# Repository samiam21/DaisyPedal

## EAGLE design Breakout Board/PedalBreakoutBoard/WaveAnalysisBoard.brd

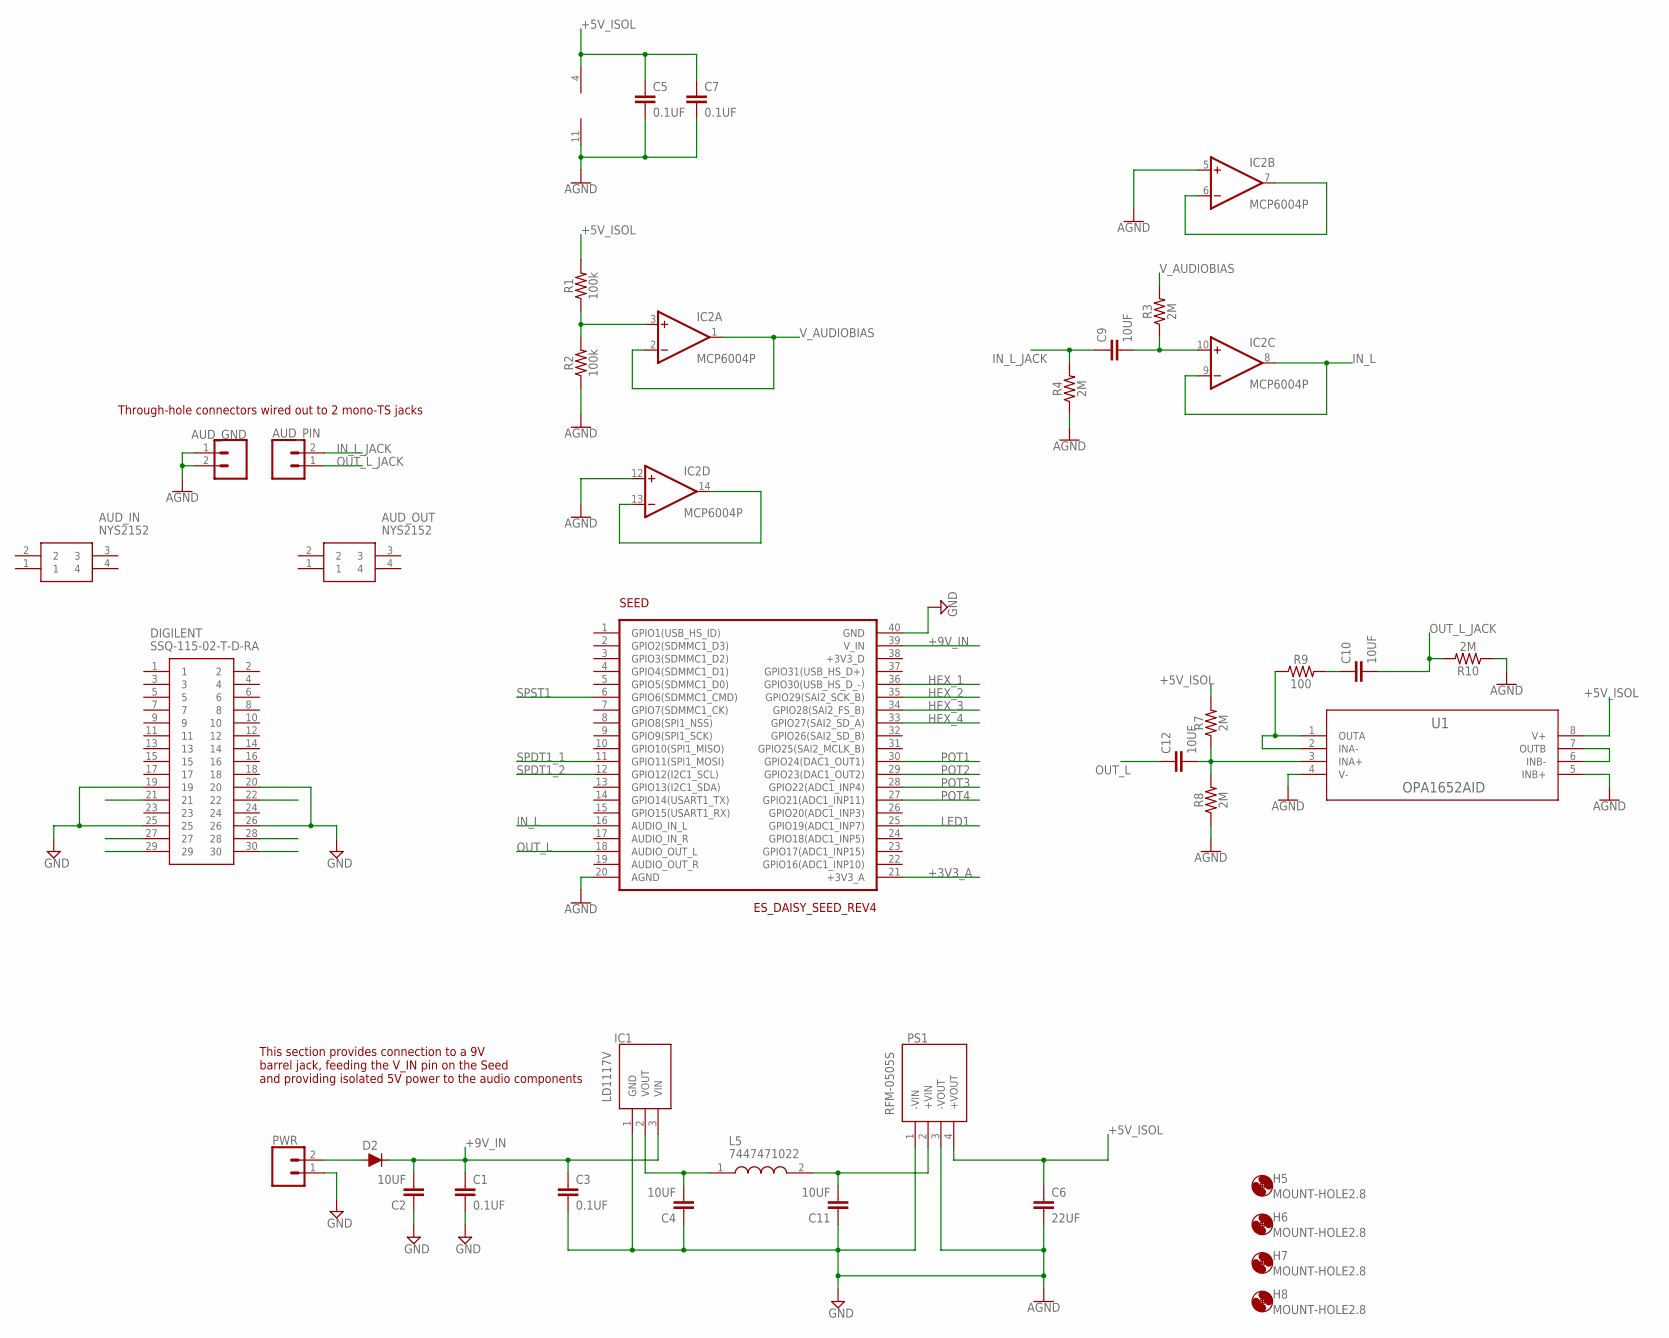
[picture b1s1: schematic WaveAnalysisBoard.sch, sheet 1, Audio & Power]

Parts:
AUD_GND: CONN_02; 1X02
AUD_IN: NYS2152
AUD_OUT: NYS2152
AUD_PIN: CONN_02; 1X02
C1, C3, C5, C7: 0.1UF; CAP-PTH-SMALL-KIT
C2, C4, C9, C10, C11, C12: 10UF; CAP-PTH-SMALL-KIT
C6: 22UF; CAP-PTH-SMALL-KIT
D2: 200mA/100V/1V; DIODE-1N4148
DIGILENT: SSQ-115-02-T-D-RA; RHDRRA30W64P254_2X15_3861X851X
H5, H6, H7, H8: MOUNT-HOLE2.8; 2,8
IC1: LD1117V; TO255P460X1020X2008-3P
IC2: MCP6004P; DIL14
L5: 7447471022; WE-TIS_111190
PS1: RFM-0505S; RFM0505S
PWR: CONN_02; 1X02
R1, R2: 100k; AXIAL-0.3
R3, R4, R7, R8, R10: 2M; AXIAL-0.3
R9: 100; AXIAL-0.3
SEED: ES_DAISY_SEED_REV4; ES_DAISY_SEED
U1: OPA1652AID; D8

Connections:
+3V3_A: SEED.21 (+3V3_A); also elsewhere on the board
+5V_ISOL: C5.1, C6.1, C7.1, IC2.4 (V+), PS1.4 (+VOUT), R1.P$2 (2), R7.P$2 (2), U1.8 (V+)
+9V_IN: C1.1, C2.2, C3.1, D2.C, IC1.3 (VIN), SEED.39 (V_IN)
AGND: AUD_GND.1, AUD_GND.2, C3.2, C4.1, C5.2, C6.2, C7.2, C11.1, IC1.1 (GND), IC2.5 (+IN), IC2.11 (V-), IC2.12 (+IN), PS1.1 (-VIN), PS1.3 (-VOUT), R2.P$1 (1), R4.P$1 (1), R8.P$1 (1), R10.P$1 (1), SEED.20 (AGND), U1.4 (V-), U1.5 (INB+)
GND: C1.2, C2.1, DIGILENT.19, DIGILENT.20, DIGILENT.25, DIGILENT.26, PWR.1, SEED.40 (GND); also elsewhere on the board
HEX_1: SEED.36 (GPIO30(USB_HS_D_-)); also elsewhere on the board
HEX_2: SEED.35 (GPIO29(SAI2_SCK_B)); also elsewhere on the board
HEX_3: SEED.34 (GPIO28(SAI2_FS_B)); also elsewhere on the board
HEX_4: SEED.33 (GPIO27(SAI2_SD_A)); also elsewhere on the board
IN_L: IC2.8 (OUT), IC2.9 (-IN), SEED.16 (AUDIO_IN_L)
IN_L_JACK: AUD_PIN.2, C9.1, R4.P$2 (2)
LED1: SEED.25 (GPIO19(ADC1_INP7)); also elsewhere on the board
unnamed: D2.A, PWR.2
unnamed: IC2.3 (+IN), R1.P$1 (1), R2.P$2 (2)
unnamed: C11.2, L5.2, PS1.2 (+VIN)
unnamed: C4.2, IC1.2 (VOUT), L5.1
unnamed: C9.2, IC2.10 (+IN), R3.P$1 (1)
unnamed: IC2.13 (-IN), IC2.14 (OUT)
unnamed: C12.2, R7.P$1 (1), R8.P$2 (2), U1.3 (INA+)
unnamed: R9.P$1 (1), U1.1 (OUTA), U1.2 (INA-)
unnamed: C10.1, R9.P$2 (2)
unnamed: U1.6 (INB-), U1.7 (OUTB)
unnamed: IC2.6 (-IN), IC2.7 (OUT)
OUT_L: C12.1, SEED.18 (AUDIO_OUT_L)
OUT_L_JACK: AUD_PIN.1, C10.2, R10.P$2 (2)
POT1: SEED.30 (GPIO24(DAC1_OUT1)); also elsewhere on the board
POT2: SEED.29 (GPIO23(DAC1_OUT2)); also elsewhere on the board
POT3: SEED.28 (GPIO22(ADC1_INP4)); also elsewhere on the board
POT4: SEED.27 (GPIO21(ADC1_INP11)); also elsewhere on the board
SPDT1_1: SEED.11 (GPIO11(SPI1_MOSI)); also elsewhere on the board
SPDT1_2: SEED.12 (GPIO12(I2C1_SCL)); also elsewhere on the board
SPST1: SEED.6 (GPIO6(SDMMC1_CMD)); also elsewhere on the board
V_AUDIOBIAS: IC2.1 (OUT), IC2.2 (-IN), R3.P$2 (2)

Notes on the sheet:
Through-hole connectors wired out to 2 mono-TS jacks
This section provides connection to a 9V barrel jack, feeding the V_IN pin on the Seed and providing isolated 5V power to the audio components

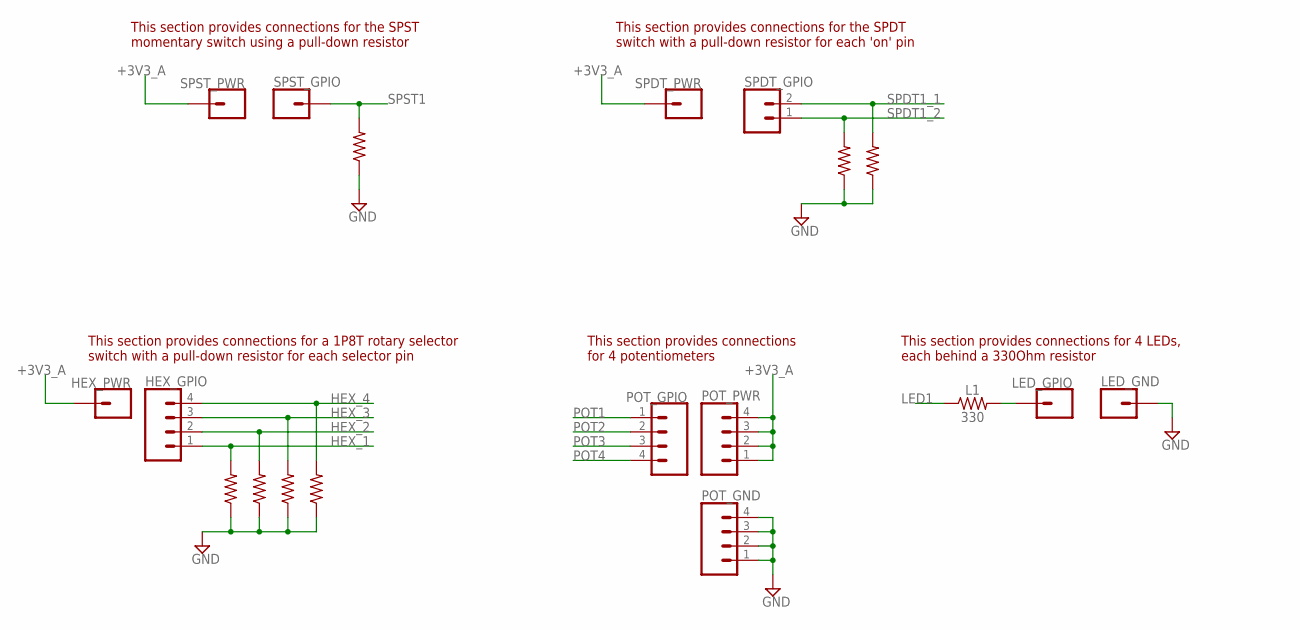
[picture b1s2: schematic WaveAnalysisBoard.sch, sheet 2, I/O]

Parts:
D11, D12: 10k; AXIAL-0.3
H1, H2, H3, H4: 10k; AXIAL-0.3
HEX_GPIO: CONN_04; 1X04
HEX_PWR: CONN_01; 1X01
L1: 330; AXIAL-0.3
LED_GND: CONN_01; 1X01
LED_GPIO: CONN_01; 1X01
POT_GND: CONN_04; 1X04
POT_GPIO: CONN_04; 1X04
POT_PWR: CONN_04; 1X04
S1: 10k; AXIAL-0.3
SPDT_GPIO: CONN_02; 1X02
SPDT_PWR: CONN_01; 1X01
SPST_GPIO: CONN_01; 1X01
SPST_PWR: CONN_01; 1X01

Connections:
+3V3_A: HEX_PWR.1, POT_PWR.1, POT_PWR.2, POT_PWR.3, POT_PWR.4, SPDT_PWR.1, SPST_PWR.1; also elsewhere on the board
GND: D11.P$1 (1), D12.P$1 (1), H1.P$1 (1), H2.P$1 (1), H3.P$1 (1), H4.P$1 (1), LED_GND.1, POT_GND.1, POT_GND.2, POT_GND.3, POT_GND.4, S1.P$1 (1); also elsewhere on the board
HEX_1: H1.P$2 (2), HEX_GPIO.1; also elsewhere on the board
HEX_2: H2.P$2 (2), HEX_GPIO.2; also elsewhere on the board
HEX_3: H3.P$2 (2), HEX_GPIO.3; also elsewhere on the board
HEX_4: H4.P$2 (2), HEX_GPIO.4; also elsewhere on the board
LED1: L1.P$1 (1); also elsewhere on the board
unnamed: L1.P$2 (2), LED_GPIO.1
POT1: POT_GPIO.1; also elsewhere on the board
POT2: POT_GPIO.2; also elsewhere on the board
POT3: POT_GPIO.3; also elsewhere on the board
POT4: POT_GPIO.4; also elsewhere on the board
SPDT1_1: D11.P$2 (2), SPDT_GPIO.2; also elsewhere on the board
SPDT1_2: D12.P$2 (2), SPDT_GPIO.1; also elsewhere on the board
SPST1: S1.P$2 (2), SPST_GPIO.1; also elsewhere on the board

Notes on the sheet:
This section provides connections for the SPDT switch with a pull-down resistor for each 'on' pin
This section provides connections for a 1P8T rotary selector switch with a pull-down resistor for each selector pin
This section provides connections for 4 potentiometers
This section provides connections for the SPST momentary switch using a pull-down resistor
This section provides connections for 4 LEDs, each behind a 330Ohm resistor

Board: 2 copper layers, 55 parts (0 on the bottom side), 34 nets, no tracks yet.

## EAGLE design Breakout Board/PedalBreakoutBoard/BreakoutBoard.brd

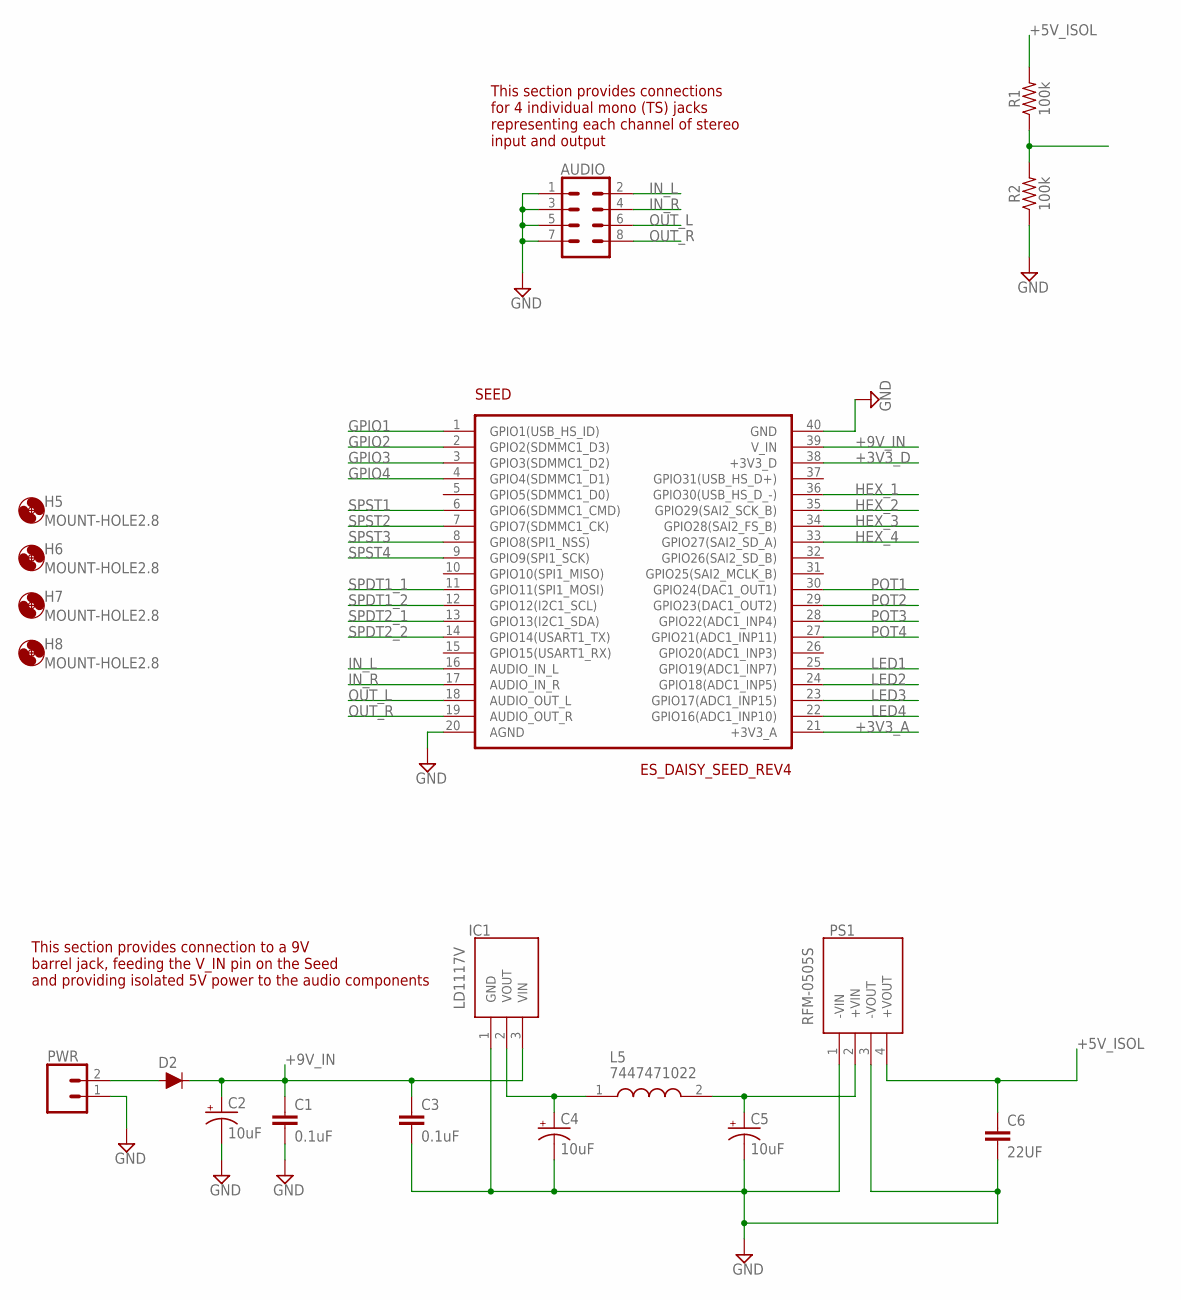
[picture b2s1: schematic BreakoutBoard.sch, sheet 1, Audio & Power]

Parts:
AUDIO: CONN_04X2; 2X4
C1, C3: 0.1uF; CAP-PTH-SMALL-KIT
C2, C4, C5: 10uF; CPOL-RADIAL-2.5MM-5MM
C6: 22UF; CAP-PTH-SMALL-KIT
D2: 200mA/100V/1V; DIODE-1N4148
H5, H6, H7, H8: MOUNT-HOLE2.8; 2,8
IC1: LD1117V; TO255P460X1020X2008-3P
L5: 7447471022; WE-TIS_111190
PS1: RFM-0505S; RFM0505S
PWR: CONN_02; 1X02
R1, R2: 100k; AXIAL-0.3
SEED: ES_DAISY_SEED_REV4; ES_DAISY_SEED

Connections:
+3V3_A: SEED.21 (+3V3_A); also elsewhere on the board
+3V3_D: SEED.38 (+3V3_D)
+5V_ISOL: C6.1, PS1.4 (+VOUT), R1.P$2 (2)
+9V_IN: C1.1, C2.1 (+), C3.1, D2.C, IC1.3 (VIN), SEED.39 (V_IN)
GND: AUDIO.1, AUDIO.3, AUDIO.5, AUDIO.7, C1.2, C2.2 (-), C3.2, C4.2 (-), C5.2 (-), C6.2, IC1.1 (GND), PS1.1 (-VIN), PS1.3 (-VOUT), PWR.1, R2.P$1 (1), SEED.20 (AGND), SEED.40 (GND); also elsewhere on the board
GPIO1: SEED.1 (GPIO1(USB_HS_ID)); also elsewhere on the board
GPIO2: SEED.2 (GPIO2(SDMMC1_D3)); also elsewhere on the board
GPIO3: SEED.3 (GPIO3(SDMMC1_D2)); also elsewhere on the board
GPIO4: SEED.4 (GPIO4(SDMMC1_D1)); also elsewhere on the board
HEX_1: SEED.36 (GPIO30(USB_HS_D_-)); also elsewhere on the board
HEX_2: SEED.35 (GPIO29(SAI2_SCK_B)); also elsewhere on the board
HEX_3: SEED.34 (GPIO28(SAI2_FS_B)); also elsewhere on the board
HEX_4: SEED.33 (GPIO27(SAI2_SD_A)); also elsewhere on the board
IN_L: AUDIO.2, SEED.16 (AUDIO_IN_L)
IN_R: AUDIO.4, SEED.17 (AUDIO_IN_R)
LED1: SEED.25 (GPIO19(ADC1_INP7)); also elsewhere on the board
LED2: SEED.24 (GPIO18(ADC1_INP5)); also elsewhere on the board
LED3: SEED.23 (GPIO17(ADC1_INP15)); also elsewhere on the board
LED4: SEED.22 (GPIO16(ADC1_INP10)); also elsewhere on the board
unnamed: D2.A, PWR.2
unnamed: R1.P$1 (1), R2.P$2 (2)
unnamed: C5.1 (+), L5.2, PS1.2 (+VIN)
unnamed: C4.1 (+), IC1.2 (VOUT), L5.1
OUT_L: AUDIO.6, SEED.18 (AUDIO_OUT_L)
OUT_R: AUDIO.8, SEED.19 (AUDIO_OUT_R)
POT1: SEED.30 (GPIO24(DAC1_OUT1)); also elsewhere on the board
POT2: SEED.29 (GPIO23(DAC1_OUT2)); also elsewhere on the board
POT3: SEED.28 (GPIO22(ADC1_INP4)); also elsewhere on the board
POT4: SEED.27 (GPIO21(ADC1_INP11)); also elsewhere on the board
SPDT1_1: SEED.11 (GPIO11(SPI1_MOSI)); also elsewhere on the board
SPDT1_2: SEED.12 (GPIO12(I2C1_SCL)); also elsewhere on the board
SPDT2_1: SEED.13 (GPIO13(I2C1_SDA)); also elsewhere on the board
SPDT2_2: SEED.14 (GPIO14(USART1_TX)); also elsewhere on the board
SPST1: SEED.6 (GPIO6(SDMMC1_CMD)); also elsewhere on the board
SPST2: SEED.7 (GPIO7(SDMMC1_CK)); also elsewhere on the board
SPST3: SEED.8 (GPIO8(SPI1_NSS)); also elsewhere on the board
SPST4: SEED.9 (GPIO9(SPI1_SCK)); also elsewhere on the board

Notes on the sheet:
This section provides connections for 4 individual mono (TS) jacks representing each channel of stereo input and output
This section provides connection to a 9V barrel jack, feeding the V_IN pin on the Seed and providing isolated 5V power to the audio components

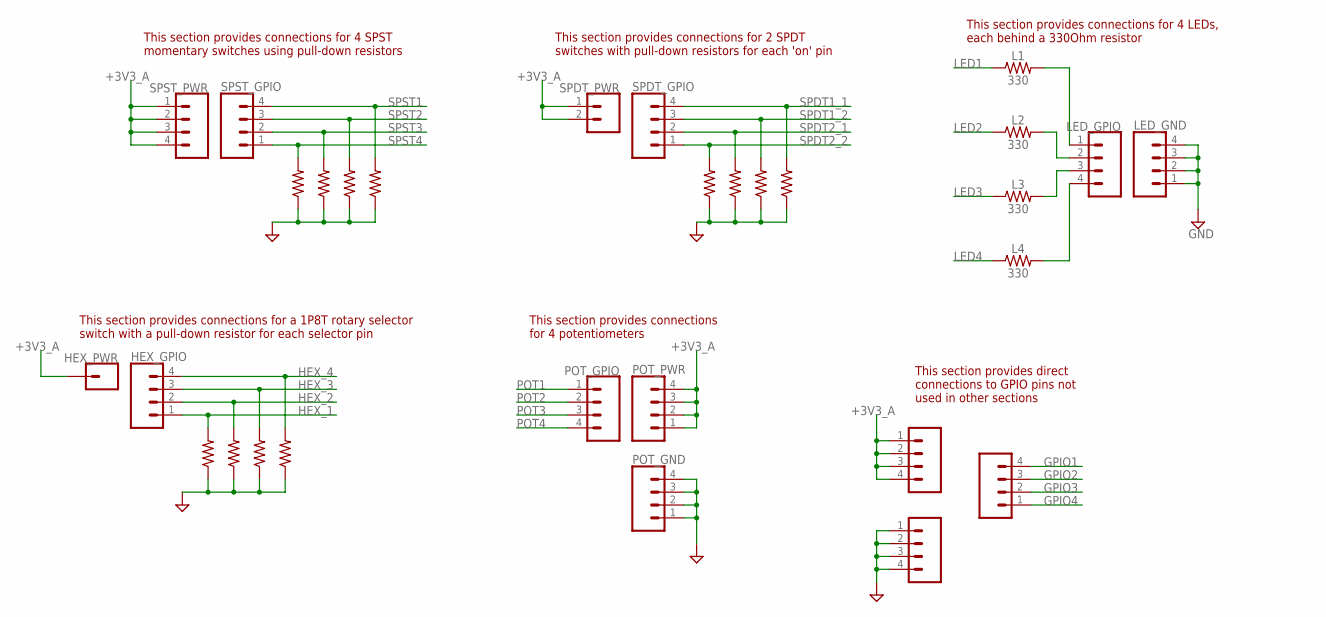
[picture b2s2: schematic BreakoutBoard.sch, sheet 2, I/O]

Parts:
D11, D12, D21, D22: 10k; AXIAL-0.3
EX_GND: CONN_04; 1X04
EX_GPIOS: CONN_04; 1X04
EX_PWR: CONN_04; 1X04
H1, H2, H3, H4: 10k; AXIAL-0.3
HEX_GPIO: CONN_04; 1X04
HEX_PWR: CONN_01; 1X01
L1, L2, L3, L4: 330; AXIAL-0.3
LED_GND: CONN_04; 1X04
LED_GPIO: CONN_04; 1X04
POT_GND: CONN_04; 1X04
POT_GPIO: CONN_04; 1X04
POT_PWR: CONN_04; 1X04
S1, S2, S3, S4: 10k; AXIAL-0.3
SPDT_GPIO: CONN_04; 1X04
SPDT_PWR: CONN_02; 1X02
SPST_GPIO: CONN_04; 1X04
SPST_PWR: CONN_04; 1X04

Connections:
+3V3_A: EX_PWR.1, EX_PWR.2, EX_PWR.3, EX_PWR.4, HEX_PWR.1, POT_PWR.1, POT_PWR.2, POT_PWR.3, POT_PWR.4, SPDT_PWR.1, SPDT_PWR.2, SPST_PWR.1, SPST_PWR.2, SPST_PWR.3, SPST_PWR.4; also elsewhere on the board
GND: D11.P$1 (1), D12.P$1 (1), D21.P$1 (1), D22.P$1 (1), EX_GND.1, EX_GND.2, EX_GND.3, EX_GND.4, H1.P$1 (1), H2.P$1 (1), H3.P$1 (1), H4.P$1 (1), LED_GND.1, LED_GND.2, LED_GND.3, LED_GND.4, POT_GND.1, POT_GND.2, POT_GND.3, POT_GND.4, S1.P$1 (1), S2.P$1 (1), S3.P$1 (1), S4.P$1 (1); also elsewhere on the board
GPIO1: EX_GPIOS.4; also elsewhere on the board
GPIO2: EX_GPIOS.3; also elsewhere on the board
GPIO3: EX_GPIOS.2; also elsewhere on the board
GPIO4: EX_GPIOS.1; also elsewhere on the board
HEX_1: H1.P$2 (2), HEX_GPIO.1; also elsewhere on the board
HEX_2: H2.P$2 (2), HEX_GPIO.2; also elsewhere on the board
HEX_3: H3.P$2 (2), HEX_GPIO.3; also elsewhere on the board
HEX_4: H4.P$2 (2), HEX_GPIO.4; also elsewhere on the board
LED1: L1.P$1 (1); also elsewhere on the board
LED2: L2.P$1 (1); also elsewhere on the board
LED3: L3.P$1 (1); also elsewhere on the board
LED4: L4.P$1 (1); also elsewhere on the board
unnamed: L1.P$2 (2), LED_GPIO.1
unnamed: L2.P$2 (2), LED_GPIO.2
unnamed: L3.P$2 (2), LED_GPIO.3
unnamed: L4.P$2 (2), LED_GPIO.4
POT1: POT_GPIO.1; also elsewhere on the board
POT2: POT_GPIO.2; also elsewhere on the board
POT3: POT_GPIO.3; also elsewhere on the board
POT4: POT_GPIO.4; also elsewhere on the board
SPDT1_1: D11.P$2 (2), SPDT_GPIO.4; also elsewhere on the board
SPDT1_2: D12.P$2 (2), SPDT_GPIO.3; also elsewhere on the board
SPDT2_1: D21.P$2 (2), SPDT_GPIO.2; also elsewhere on the board
SPDT2_2: D22.P$2 (2), SPDT_GPIO.1; also elsewhere on the board
SPST1: S1.P$2 (2), SPST_GPIO.4; also elsewhere on the board
SPST2: S2.P$2 (2), SPST_GPIO.3; also elsewhere on the board
SPST3: S3.P$2 (2), SPST_GPIO.2; also elsewhere on the board
SPST4: S4.P$2 (2), SPST_GPIO.1; also elsewhere on the board

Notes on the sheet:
This section provides connections for 2 SPDT switches with pull-down resistors for each 'on' pin
This section provides connections for a 1P8T rotary selector switch with a pull-down resistor for each selector pin
This section provides connections for 4 potentiometers
This section provides connections for 4 SPST momentary switches using pull-down resistors
This section provides connections for 4 LEDs, each behind a 330Ohm resistor
This section provides direct connections to GPIO pins not used in other sections

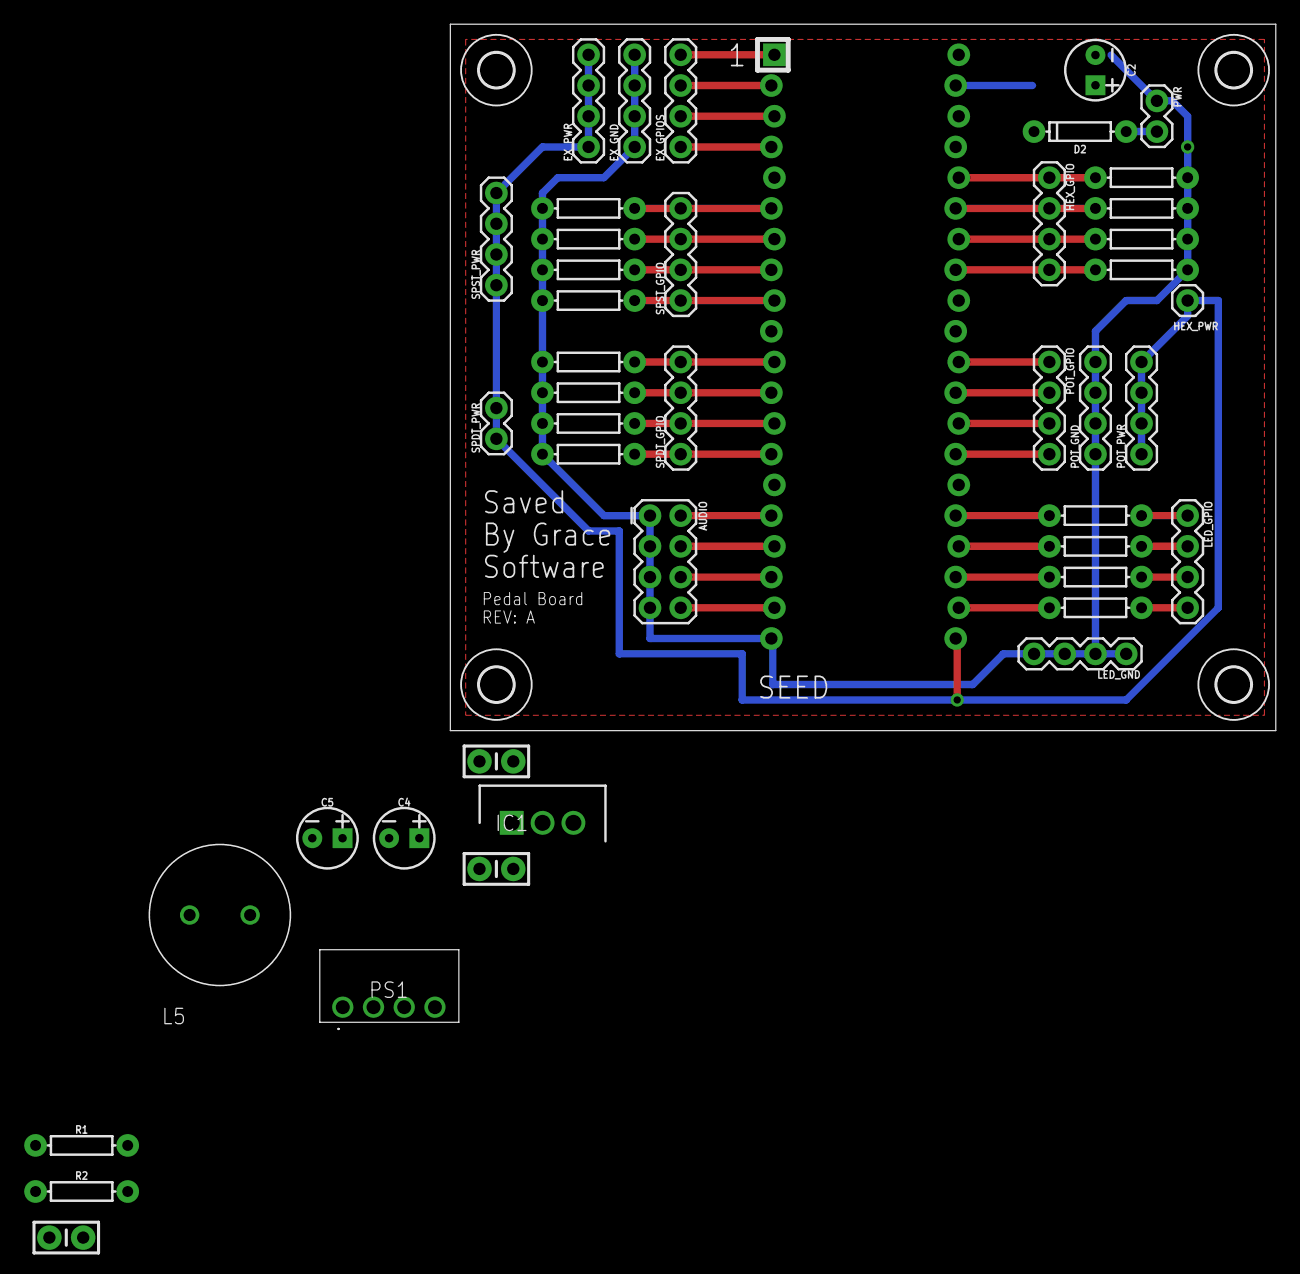
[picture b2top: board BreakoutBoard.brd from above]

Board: 2 copper layers, 68.2 x 58.4 mm, 49 parts (0 on the bottom side), 40 nets.

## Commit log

2020-09-08 DP-9 - Add StereoDelay example
2020-09-08 DP-9 - Stereo delay disabled with button press
2020-09-08 DP-9 - Add bypass example and mono starting point
2020-09-08 DP-9 - Update mono to use single channel
2020-09-11 DP-9 - Add audacity test project
2020-09-20 DP-9 - Fix issue with long verify times
2020-09-20 DP-9 - Disable auto-formatting for this workspace
2020-09-20 DP-9 - Turn delay on/off with a switch
2020-10-01 DP-9 - Add toggle of LED for delay on/off
2020-10-01 DP-10 - Set delay tempo in BPM
2020-10-02 DP-10 - Cleanup and adding timespan formula to comments
2020-10-02 DP-12 - Add initial connectors notes
2020-10-02 DP-12 - Move testing audio into subfolder
2020-10-03 DP-12 - Add base app
2020-10-03 DP-12 - Reference mono delay from pedal app
2020-10-03 DP-12 - Enable effect based on hex switch
2020-10-03 DP-12 - Clean up mono delay
2020-10-03 DP-12 - Fix startup to enable bypass
2020-10-03 DP-12 - Update pins for switch
2020-10-07 DP-10 - Add debug serial printing
2020-10-07 DP-10 - Add button press to light LED for mono delay
2020-10-07 DP-10 - Fix hex switch reading
2020-10-08 DP-10 - Calculate time between button presses
2020-10-08 DP-10 - Add include path for desktop
2020-10-08 DP-10 - Adding tempo array class
2020-10-08 DP-10 - Working on reorganizing project structure
2020-10-09 DP-10 - Move MonoDelay files into subdirectory
2020-10-09 DP-10 - Add HWDebug effect type
2020-10-09 DP-10 - Fix calculation of tempo
2020-10-09 DP-10 - Merge bypass and hwdebug to reduce memory usage
2020-10-09 DP-10 - Code cleanup
2020-10-09 Update the README
2020-10-14 DP-11 - Add handling and testing of pots
2020-10-14 DP-11 - Working on reading decay knob
2020-10-14 DP-11 - Read decay knob
2020-10-14 DP-11 - Move decay knob reading parameter
2020-10-17 DP-11 - Adjust decay with knob
2020-10-17 DP-11 - Add possible future effect types
2020-10-17 DP-14 - Add level control
2020-10-17 DP-14 - Switch level and decay knobs
2020-10-17 DP-14 - Update comments
2020-10-17 DP-15 - Add definitions in comments
2020-10-18 DP-16 - Add base project and daisy library
2020-10-18 DP-16 - Add empty schematic
2020-10-19 DP-16 - Adding audio connectors
2020-10-19 DP-16 - Add grounds
2020-10-19 DP-16 - Add audio molex
2020-10-19 DP-16 - Add LED molex
2020-10-19 DP-16 - Update LED molex
2020-10-19 DP-16 - Add SPST molex
2020-10-19 DP-16 - Update board in/out
2020-10-19 DP-16 - Change molex connectors to through holes
2020-10-19 DP-16 - Move connections into groups
2020-10-19 DP-16 - Add SPDT section
2020-10-19 DP-16 - Reorder groups for consistency
2020-10-20 DP-16 - Add selector section
2020-10-21 DP-16 - Update schematic to add new sheet
2020-10-21 DP-16 - Update schematic with correct 3V3 feeds
2020-10-21 DP-16 - Add power section
2020-10-21 DP-16 - Fix nets
2020-10-21 DP-16 - Working on board layout
2020-10-22 DP-16 - Board layout REV-A
2020-10-22 DP-16 - Board layout REV-B
2020-10-22 DP-16 - Initial routing
2020-10-22 DP-16 - Update board layout
2020-10-22 DP-16 - Working on silkscreen and mounting holes
2020-10-22 DP-16 - Updating to through hole parts
2020-10-22 DP-16 - Update firmware to handle gray coded rotary switch
2020-10-22 Working on adding mounting holes
2020-10-23 DP-16 - Update capacitors to through hole components
2020-10-25 DP-16 - Add mounting holes
2020-10-26 DP-16 - Move Daisy to edge
2020-10-26 DP-16 - Shrink board
2020-10-26 DP-15 - Updating pin definitions
2020-10-27 DP-15 - Update pin definitions
2020-10-27 DP-15 - Add example of using a class function as the daisy callback
2020-10-28 DP-15 - Convert effects to classes
2020-10-28 DP-15 - Use effect interface for pedal loop
2020-10-28 DP-15 - Add SPDT test to bypass
2020-10-28 DP-15 - Remove monodelay to make this a template
2020-10-28 DP-20 - Update copper pour
2020-10-28 DP-20 - Move covered label
2020-11-05 Remove putty link
2020-11-11 Convert to platformio
2020-11-11 DP-24 - Working on converting to interrupts
2020-11-12 DP-24 - Change selector to interrupt and fix serial printing
2020-11-12 Auto-update of cpp properties by platform io
2020-11-18 Updating pinout to match new pcb
2020-11-18 Fix encoder reading
2020-11-18 Fix selector interrupts
2020-11-19 Add ability to bypass effect selector
2020-11-19 Fix bypassing of effect selector
2020-11-20 Ignoring .vscode files
2020-11-22 Add knob class
2020-11-23 Fix knob class
2020-11-24 Add button handler class
2020-11-24 Update HWTest to use button and knob classes
2020-11-24 Add toggle class
2020-12-08 DP-33 - Added power section
2020-12-08 DP-33 - Add custom library and 22uf capacitor
2020-12-08 DP-33 - Add remaining audio noise schematic
2020-12-08 DP-33 - Add MonoPedal schematic
2020-12-08 DP-33 - Ignore backup files for Eagle
2020-12-08 DP-34 - Working on board layout
2020-12-10 Working on board layout
2020-12-10 DP-34 - First draft board layout complete
2020-12-10 DP-34 - Fixing silk screen errors
2020-12-11 DP-35 - Fix selector by switching back to polling
2020-12-23 DP-33 - Update breakout board with ceramic capacitors
2020-12-23 DP-33 - Update mono pedal to ceramic 10uF capacitors
2020-12-23 DP-33 - Update mono pedal board with proper silk screen
2020-12-23 DP-33 - Add BOM for mono pedal
2021-01-08 Add ability to upload directly through USB
2021-01-08 Add ability to set block size to help minimize noise
2021-01-15 Update audio pins to work with new board
2021-02-28 DP-6 - Add multi-effect project and update encoder pins
2021-02-28 DP-6 - Add connections for OLED
2021-02-28 DP-6 - Add additional POT for output volume
2021-02-28 DP-6 - Add additional LEDs
2021-02-28 DP-6 - Re-layout of audio noise reduction circuit
2021-02-28 DP-6 - Add additional SPST connections
2021-02-28 DP-6 - Board cleanup
2021-03-01 DP-6 - Add grounding plane
2021-03-01 DP-6 - Add additional access to GPIO pins
2021-03-01 DP-6 - Add logo to board
2021-08-17 DP-97 - Add schematic for wave analysis board
2021-08-17 DP-97 - Add header component
2021-08-18 DP-97 - Working on adding header
2021-08-23 DP-97 - Moved PCB to PedalPCB repo
2021-09-29 DP-97 - Update multi-effect with new grounding scheme

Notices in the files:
parts and their libraries:
SparkFun-Connectors: Licensing: Creative Commons ShareAlike 4.0 International - https://creativecommons.org/licenses/by-sa/4.0
